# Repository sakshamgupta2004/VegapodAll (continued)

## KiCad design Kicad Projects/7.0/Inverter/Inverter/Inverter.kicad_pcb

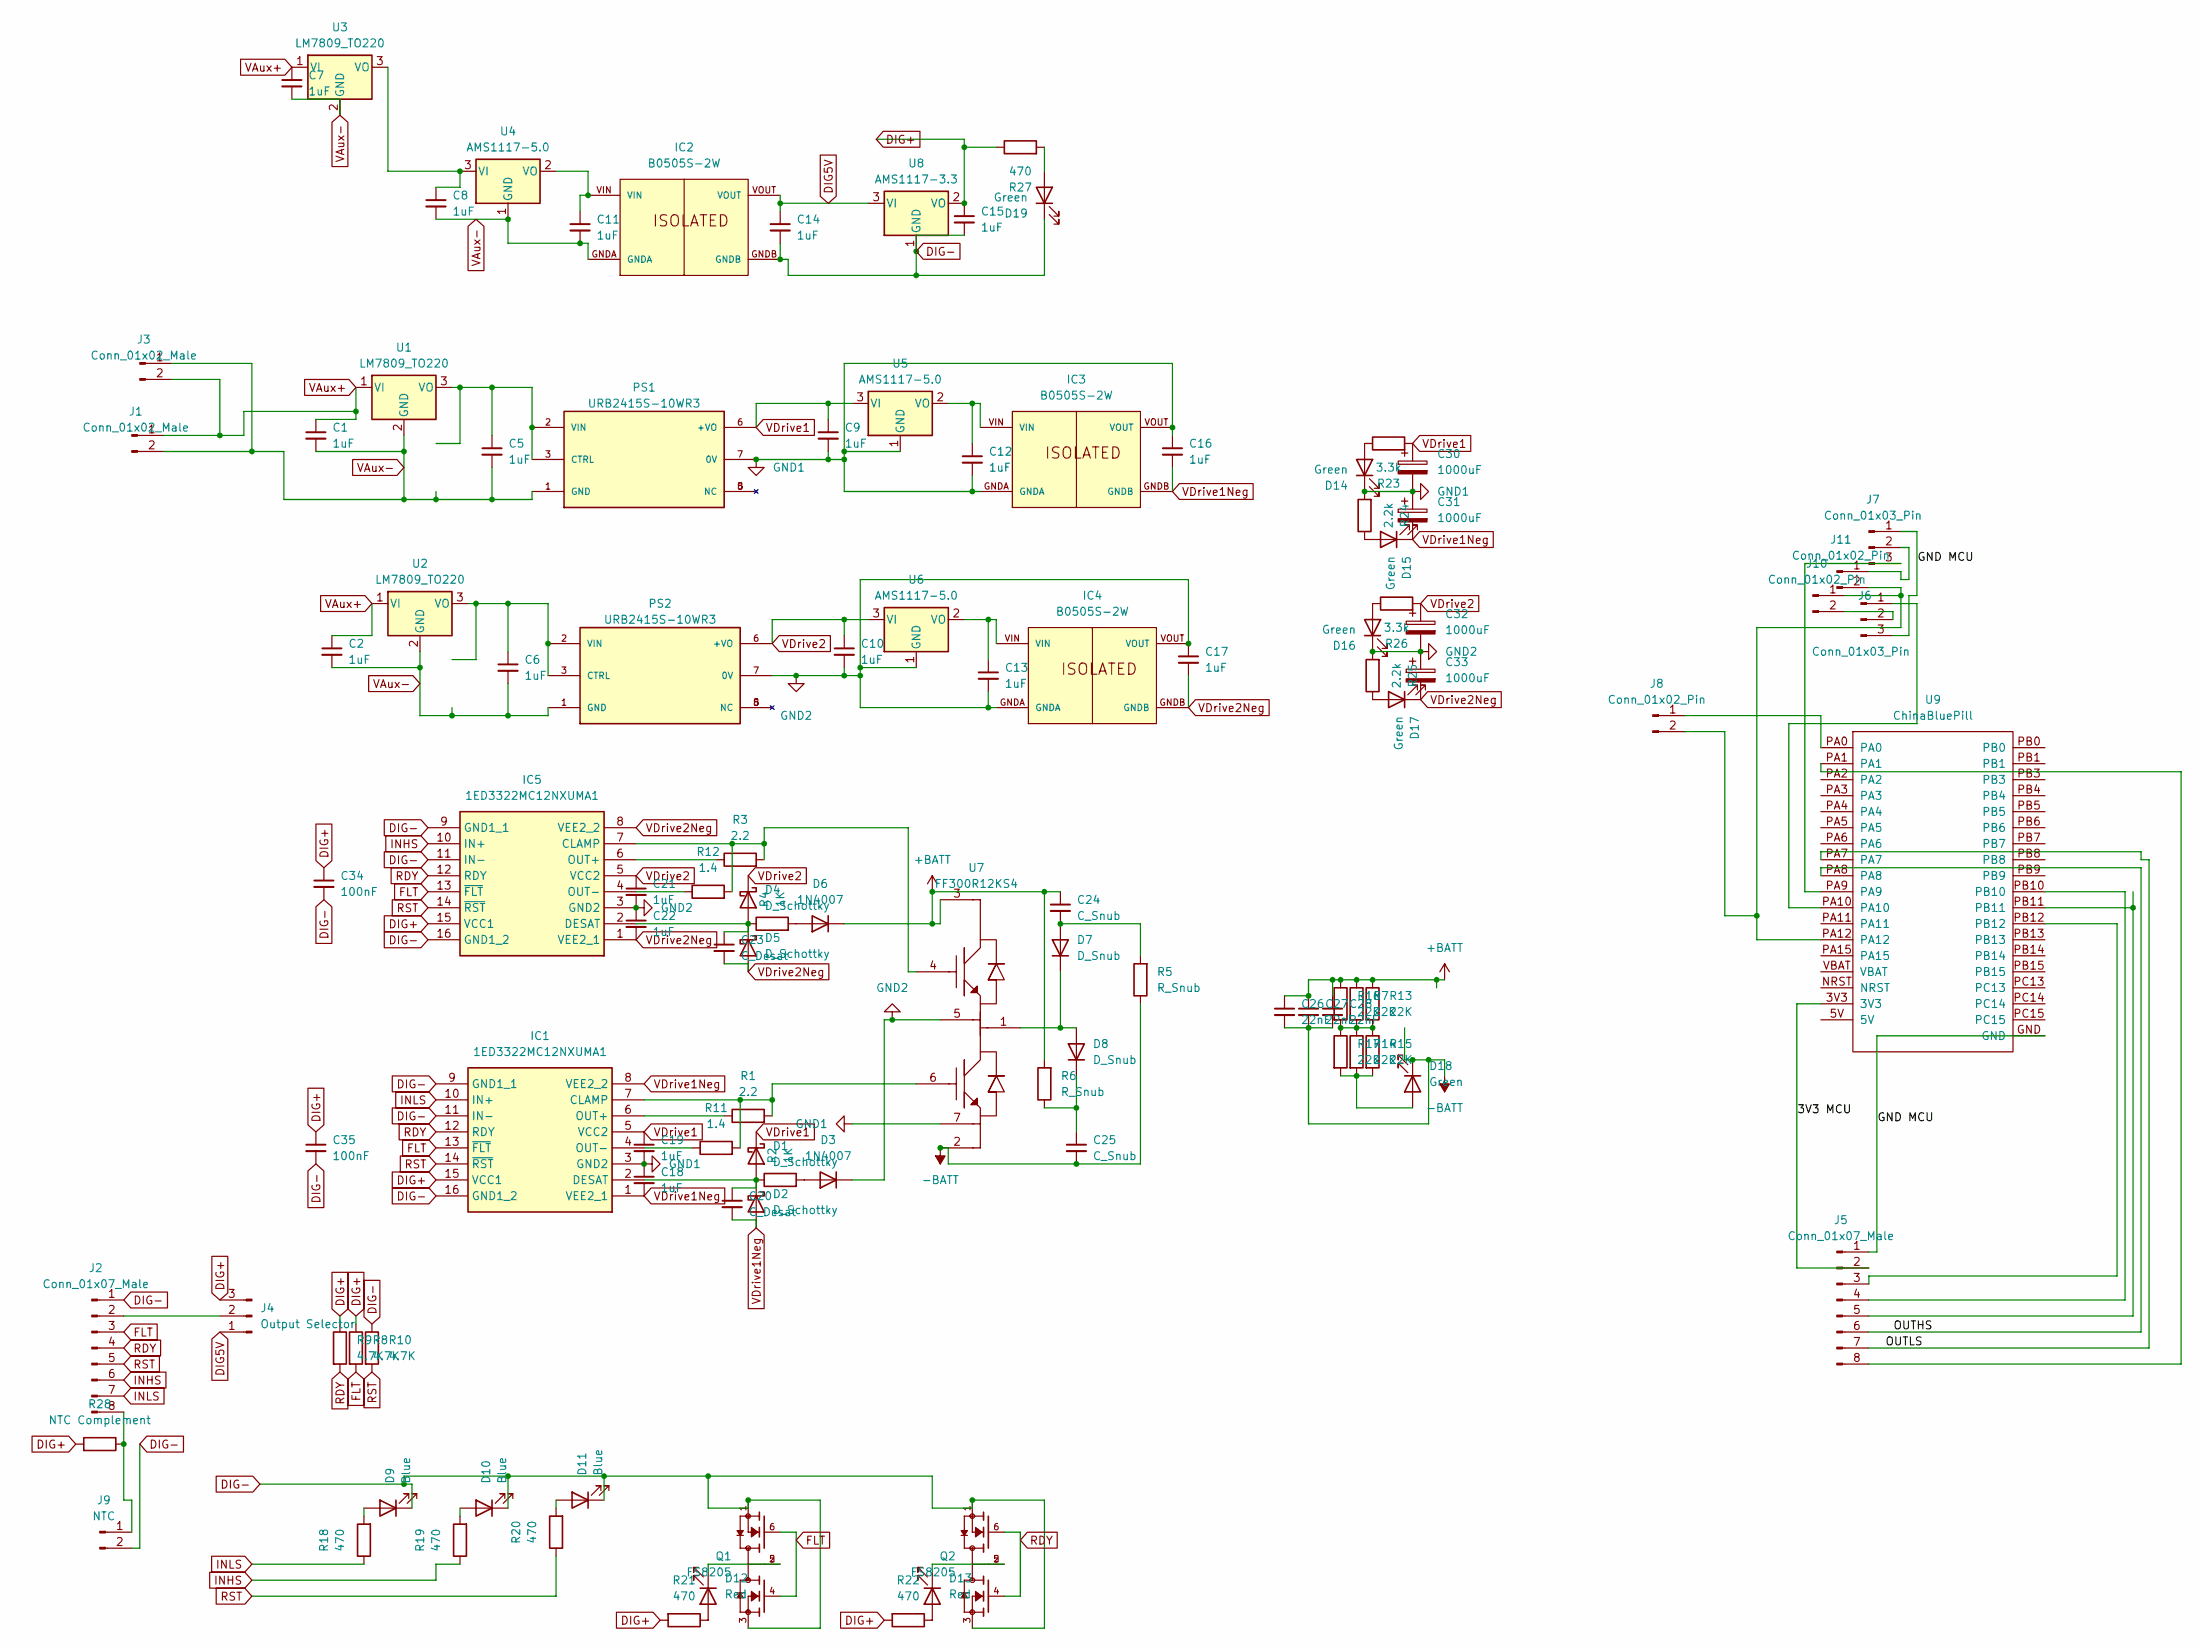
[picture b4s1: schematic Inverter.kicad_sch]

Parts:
C1, C2, C5, C6, C7, C8, C9, C10, C11, C12, C13, C14, C15, C16, C17, C18, C19, C21, C22: 1uF; C_1206_3216Metric_Pad1.33x1.80mm_HandSolder
C20, C23: C_Desat; C_0603_1608Metric_Pad1.08x0.95mm_HandSolder
C24, C25: C_Snub; C_Rect_L24.0mm_W8.3mm_P22.50mm_MKT
C26, C27, C28: 22nF; C_1206_3216Metric_Pad1.33x1.80mm_HandSolder
C30, C31, C32, C33: 1000uF; CAP_EEEFK1E102AQ
C34, C35: 100nF; C_0603_1608Metric_Pad1.08x0.95mm_HandSolder
D1, D2, D4, D5: D_Schottky; D_SMA_Handsoldering
D3, D6: 1N4007; D_SMA_Handsoldering
D7, D8: D_Snub; D_DO-201AE_P15.24mm_Horizontal
D9, D10, D11: Blue; LED_0805_2012Metric_Pad1.15x1.40mm_HandSolder
D12, D13: Red; LED_0805_2012Metric_Pad1.15x1.40mm_HandSolder
D14, D15, D16, D17, D18, D19: Green; LED_0805_2012Metric_Pad1.15x1.40mm_HandSolder
IC1, IC5: 1ED3322MC12NXUMA1; SOIC127P1030X265-16N; Mouser Part Number 726-1ED3322MC12NXUMA
IC2, IC3, IC4: B0505S-2W; MPN B0505S-2W; DigiKey_Part_Number 2725-B0505S-2W-ND
J1, J3: Conn_01x02_Male; JST_XH_S2B-XH-A_1x02_P2.50mm_Horizontal
J2, J5: Conn_01x07_Male; JST_XH_B8B-XH-A_1x08_P2.50mm_Vertical
J4: Output Selector; PinSocket_1x03_P1.27mm_Vertical
J6, J7: Conn_01x03_Pin; JST_XH_S3B-XH-A_1x03_P2.50mm_Horizontal
J8, J10, J11: Conn_01x02_Pin; PinHeader_1x02_P1.27mm_Vertical
J9: NTC; PinHeader_1x02_P1.27mm_Vertical
PS1, PS2: URB2415S-10WR3; CONV_URB2415S-10WR3; PARTREV 2020.11.09-A/4; DigiKey_Part_Number 2725-URB2415S-10WR3-ND
Q1, Q2: FS8205; SOT95P280X145-6N; PARTREV 1.9
R1, R3: 2.2; R_0805_2012Metric_Pad1.20x1.40mm_HandSolder
R2, R4: 1K; R_0603_1608Metric_Pad0.98x0.95mm_HandSolder
R5, R6: R_Snub; R_Box_L26.0mm_W5.0mm_P20.00mm
R7, R13, R14, R15, R16, R17: 22K; R_1206_3216Metric_Pad1.30x1.75mm_HandSolder
R8, R9, R10: 4.7K; R_0805_2012Metric_Pad1.20x1.40mm_HandSolder
R11, R12: 1.4; R_0805_2012Metric_Pad1.20x1.40mm_HandSolder
R18, R19, R20, R21, R22, R27: 470; R_0603_1608Metric_Pad0.98x0.95mm_HandSolder
R23, R26: 3.3k; R_0603_1608Metric_Pad0.98x0.95mm_HandSolder
R24, R25: 2.2k; R_0603_1608Metric_Pad0.98x0.95mm_HandSolder
R28: NTC Complement; R_0805_2012Metric_Pad1.20x1.40mm_HandSolder
U1, U2, U3: LM7809_TO220; TO-220-3_Vertical
U4, U5, U6: AMS1117-5.0; SOT-223-3_TabPin2
U7: FF300R12KS4
U8: AMS1117-3.3; SOT-223-3_TabPin2
U9: ChinaBluePill

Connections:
+BATT: C24.1, C26.1, C27.1, C28.1, D6.1 (K), R6.2, R7.1, R13.1, R16.1, U7.3
-BATT: C25.2, C26.2, C27.2, C28.2, D18.1 (K), R5.1, U7.2
/3V3 MCU: J5.2, U9.3V3
/GND MCU: J5.1, J6.3, J7.1, U9.GND
/OUTHS: J5.6, U9.PA8
/OUTLS: J5.7, U9.PA7
DIG5V: C14.1, IC2.VOUT, J4.1, U8.3 (VI)
DIG+: C15.1, C34.1, C35.1, IC1.15 (VCC1), IC5.15 (VCC1), J4.3, R8.1, R9.1, R21.2, R22.2, R27.1, R28.2, U8.2 (VO)
DIG-: C14.2, C15.2, C34.2, C35.2, D9.1 (K), D10.1 (K), D11.1 (K), D19.1 (K), IC1.9 (GND1_1), IC1.11 (IN-), IC1.16 (GND1_2), IC2.GNDB, IC5.9 (GND1_1), IC5.11 (IN-), IC5.16 (GND1_2), J2.1, J9.2, Q1.1, Q1.3, Q2.1, Q2.3, R10.1, U8.1 (GND)
FLT: IC1.13 (~FLT), IC5.13 (~FLT), J2.3, Q1.4, Q1.6, R8.2
GND1: C9.2, C12.2, C16.1, C18.1, C19.2, C30.2, C31.1, D14.1 (K), IC1.3 (GND2), IC3.GNDA, IC3.VOUT, PS1.7 (0V), R24.2, U5.1 (GND), U7.7
GND2: C10.2, C13.2, C17.1, C21.2, C22.1, C32.2, C33.1, D3.1 (K), D16.1 (K), IC4.GNDA, IC4.VOUT, IC5.3 (GND2), PS2.7 (0V), R25.2, U6.1 (GND), U7.5
INHS: IC5.10 (IN+), J2.6, R19.1
INLS: IC1.10 (IN+), J2.7, R18.1
unnamed: C20.1, D1.2 (A), D2.1 (K), IC1.2 (DESAT), R2.1
unnamed: D3.2 (A), R2.2
unnamed: C23.1, D4.2 (A), D5.1 (K), IC5.2 (DESAT), R4.1
unnamed: D6.2 (A), R4.2
unnamed: C24.2, D7.2 (A), R5.2
unnamed: D7.1 (K), D8.2 (A), U7.1
unnamed: C25.1, D8.1 (K), R6.1
unnamed: D9.2 (A), R18.2
unnamed: D10.2 (A), R19.2
unnamed: D11.2 (A), R20.2
unnamed: D12.2 (A), R21.1
unnamed: D12.1 (K), Q1.2, Q1.5
unnamed: D13.2 (A), R22.1
unnamed: D13.1 (K), Q2.2, Q2.5
unnamed: D14.2 (A), R23.1
unnamed: D15.2 (A), R24.1
unnamed: D16.2 (A), R26.1
unnamed: D17.2 (A), R25.1
unnamed: D18.2 (A), R14.2, R15.2, R17.2
unnamed: D19.2 (A), R27.2
unnamed: IC1.7 (CLAMP), R1.2, R11.2, U7.6
unnamed: IC1.6 (OUT+), R1.1
unnamed: IC1.4 (OUT-), R11.1
unnamed: IC5.7 (CLAMP), R3.2, R12.2, U7.4
unnamed: IC5.6 (OUT+), R3.1
unnamed: IC5.4 (OUT-), R12.1
unnamed: J2.2, J4.2
unnamed: J2.8, J9.1, R28.1
unnamed: J5.3, U9.PB12
unnamed: J5.4, U9.PB10
unnamed: J5.5, U9.PB11
unnamed: J5.8, U9.PA1
unnamed: J6.1, U9.PA10
unnamed: J7.3, U9.PA9
unnamed: J8.1, U9.PA0
unnamed: J8.2, J10.1, J11.2, U9.PA12
unnamed: J6.2, J10.2
unnamed: J7.2, J11.1
unnamed: C5.1, PS1.2 (VIN), PS1.3 (CTRL), U1.3 (VO)
unnamed: C6.1, PS2.2 (VIN), PS2.3 (CTRL), U2.3 (VO)
unnamed: R7.2, R13.2, R14.1, R15.1, R16.2, R17.1
unnamed: C8.1, U3.3 (VO), U4.3 (VI)
unnamed: C11.1, IC2.VIN, U4.2 (VO)
unnamed: C12.1, IC3.VIN, U5.2 (VO)
unnamed: C13.1, IC4.VIN, U6.2 (VO)
RDY: IC1.12 (RDY), IC5.12 (RDY), J2.4, Q2.4, Q2.6, R9.2
RST: IC1.14 (~RST), IC5.14 (~RST), J2.5, R10.2, R20.1
VAux+: C1.1, C2.1, C7.1, J1.1, J3.2, U1.1 (VI), U2.1 (VI), U3.1 (VI)
VAux-: C1.2, C2.2, C5.2, C6.2, C7.2, C8.2, C11.2, IC2.GNDA, J1.2, J3.1, PS1.1 (GND), PS2.1 (GND), U1.2 (GND), U2.2 (GND), U3.2 (GND), U4.1 (GND)
VDrive1: C9.1, C19.1, C30.1, D1.1 (K), IC1.5 (VCC2), PS1.6 (+VO), R23.2, U5.3 (VI)
VDrive1Neg: C16.2, C18.2, C20.2, C31.2, D2.2 (A), D15.1 (K), IC1.1 (VEE2_1), IC1.8 (VEE2_2), IC3.GNDB
VDrive2: C10.1, C21.1, C32.1, D4.1 (K), IC5.5 (VCC2), PS2.6 (+VO), R26.2, U6.3 (VI)
VDrive2Neg: C17.2, C22.2, C23.2, C33.2, D5.2 (A), D17.1 (K), IC4.GNDB, IC5.1 (VEE2_1), IC5.8 (VEE2_2)

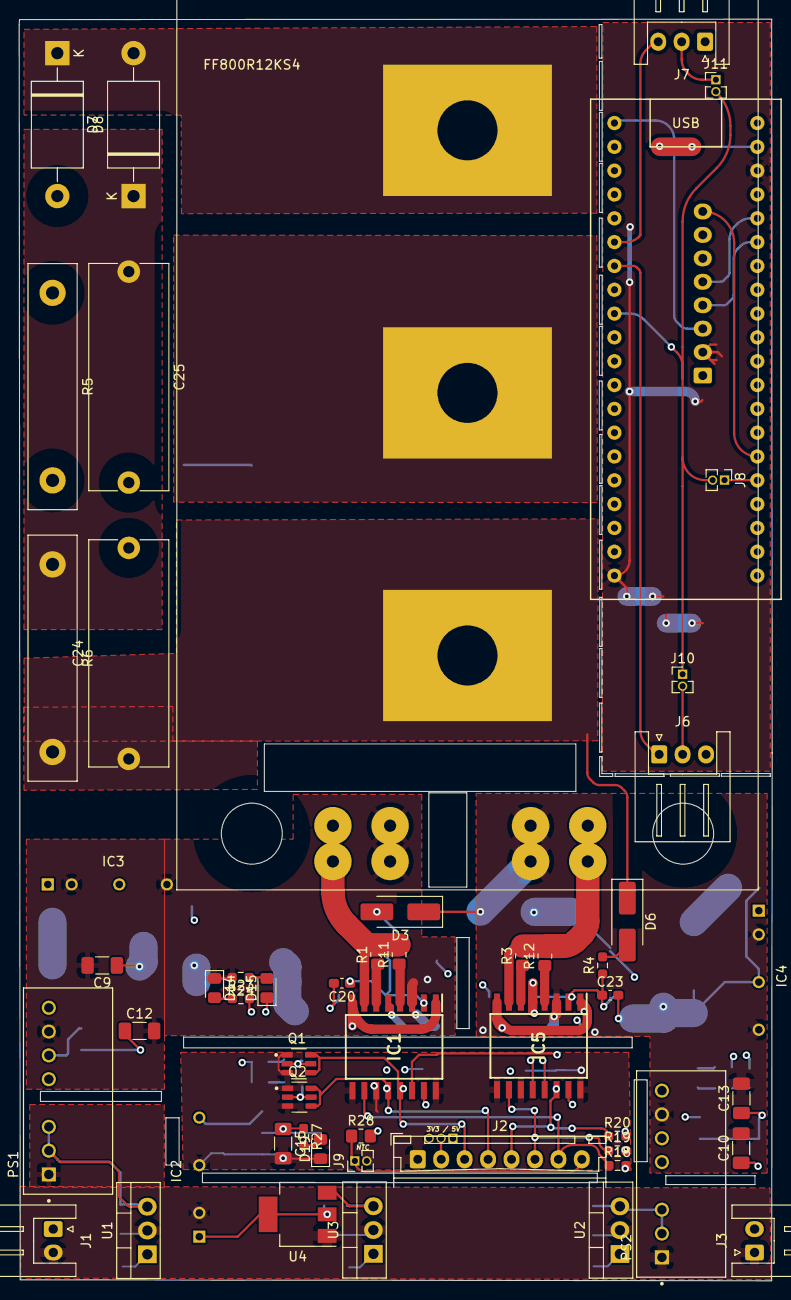
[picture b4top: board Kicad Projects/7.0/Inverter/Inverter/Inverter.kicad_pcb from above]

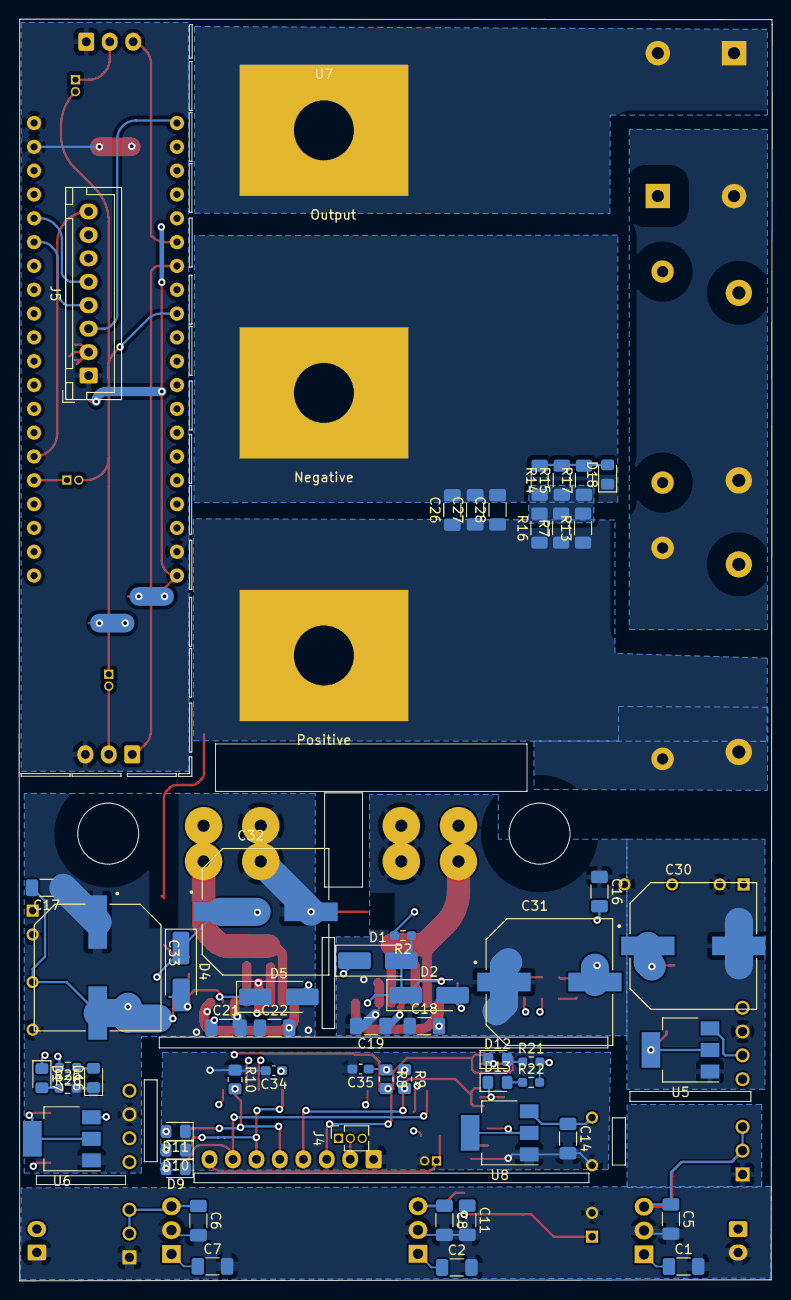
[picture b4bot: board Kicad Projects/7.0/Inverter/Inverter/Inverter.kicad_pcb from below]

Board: 4 copper layers, 80.3 x 134.5 mm, 108 parts (55 on the bottom side), 67 nets.

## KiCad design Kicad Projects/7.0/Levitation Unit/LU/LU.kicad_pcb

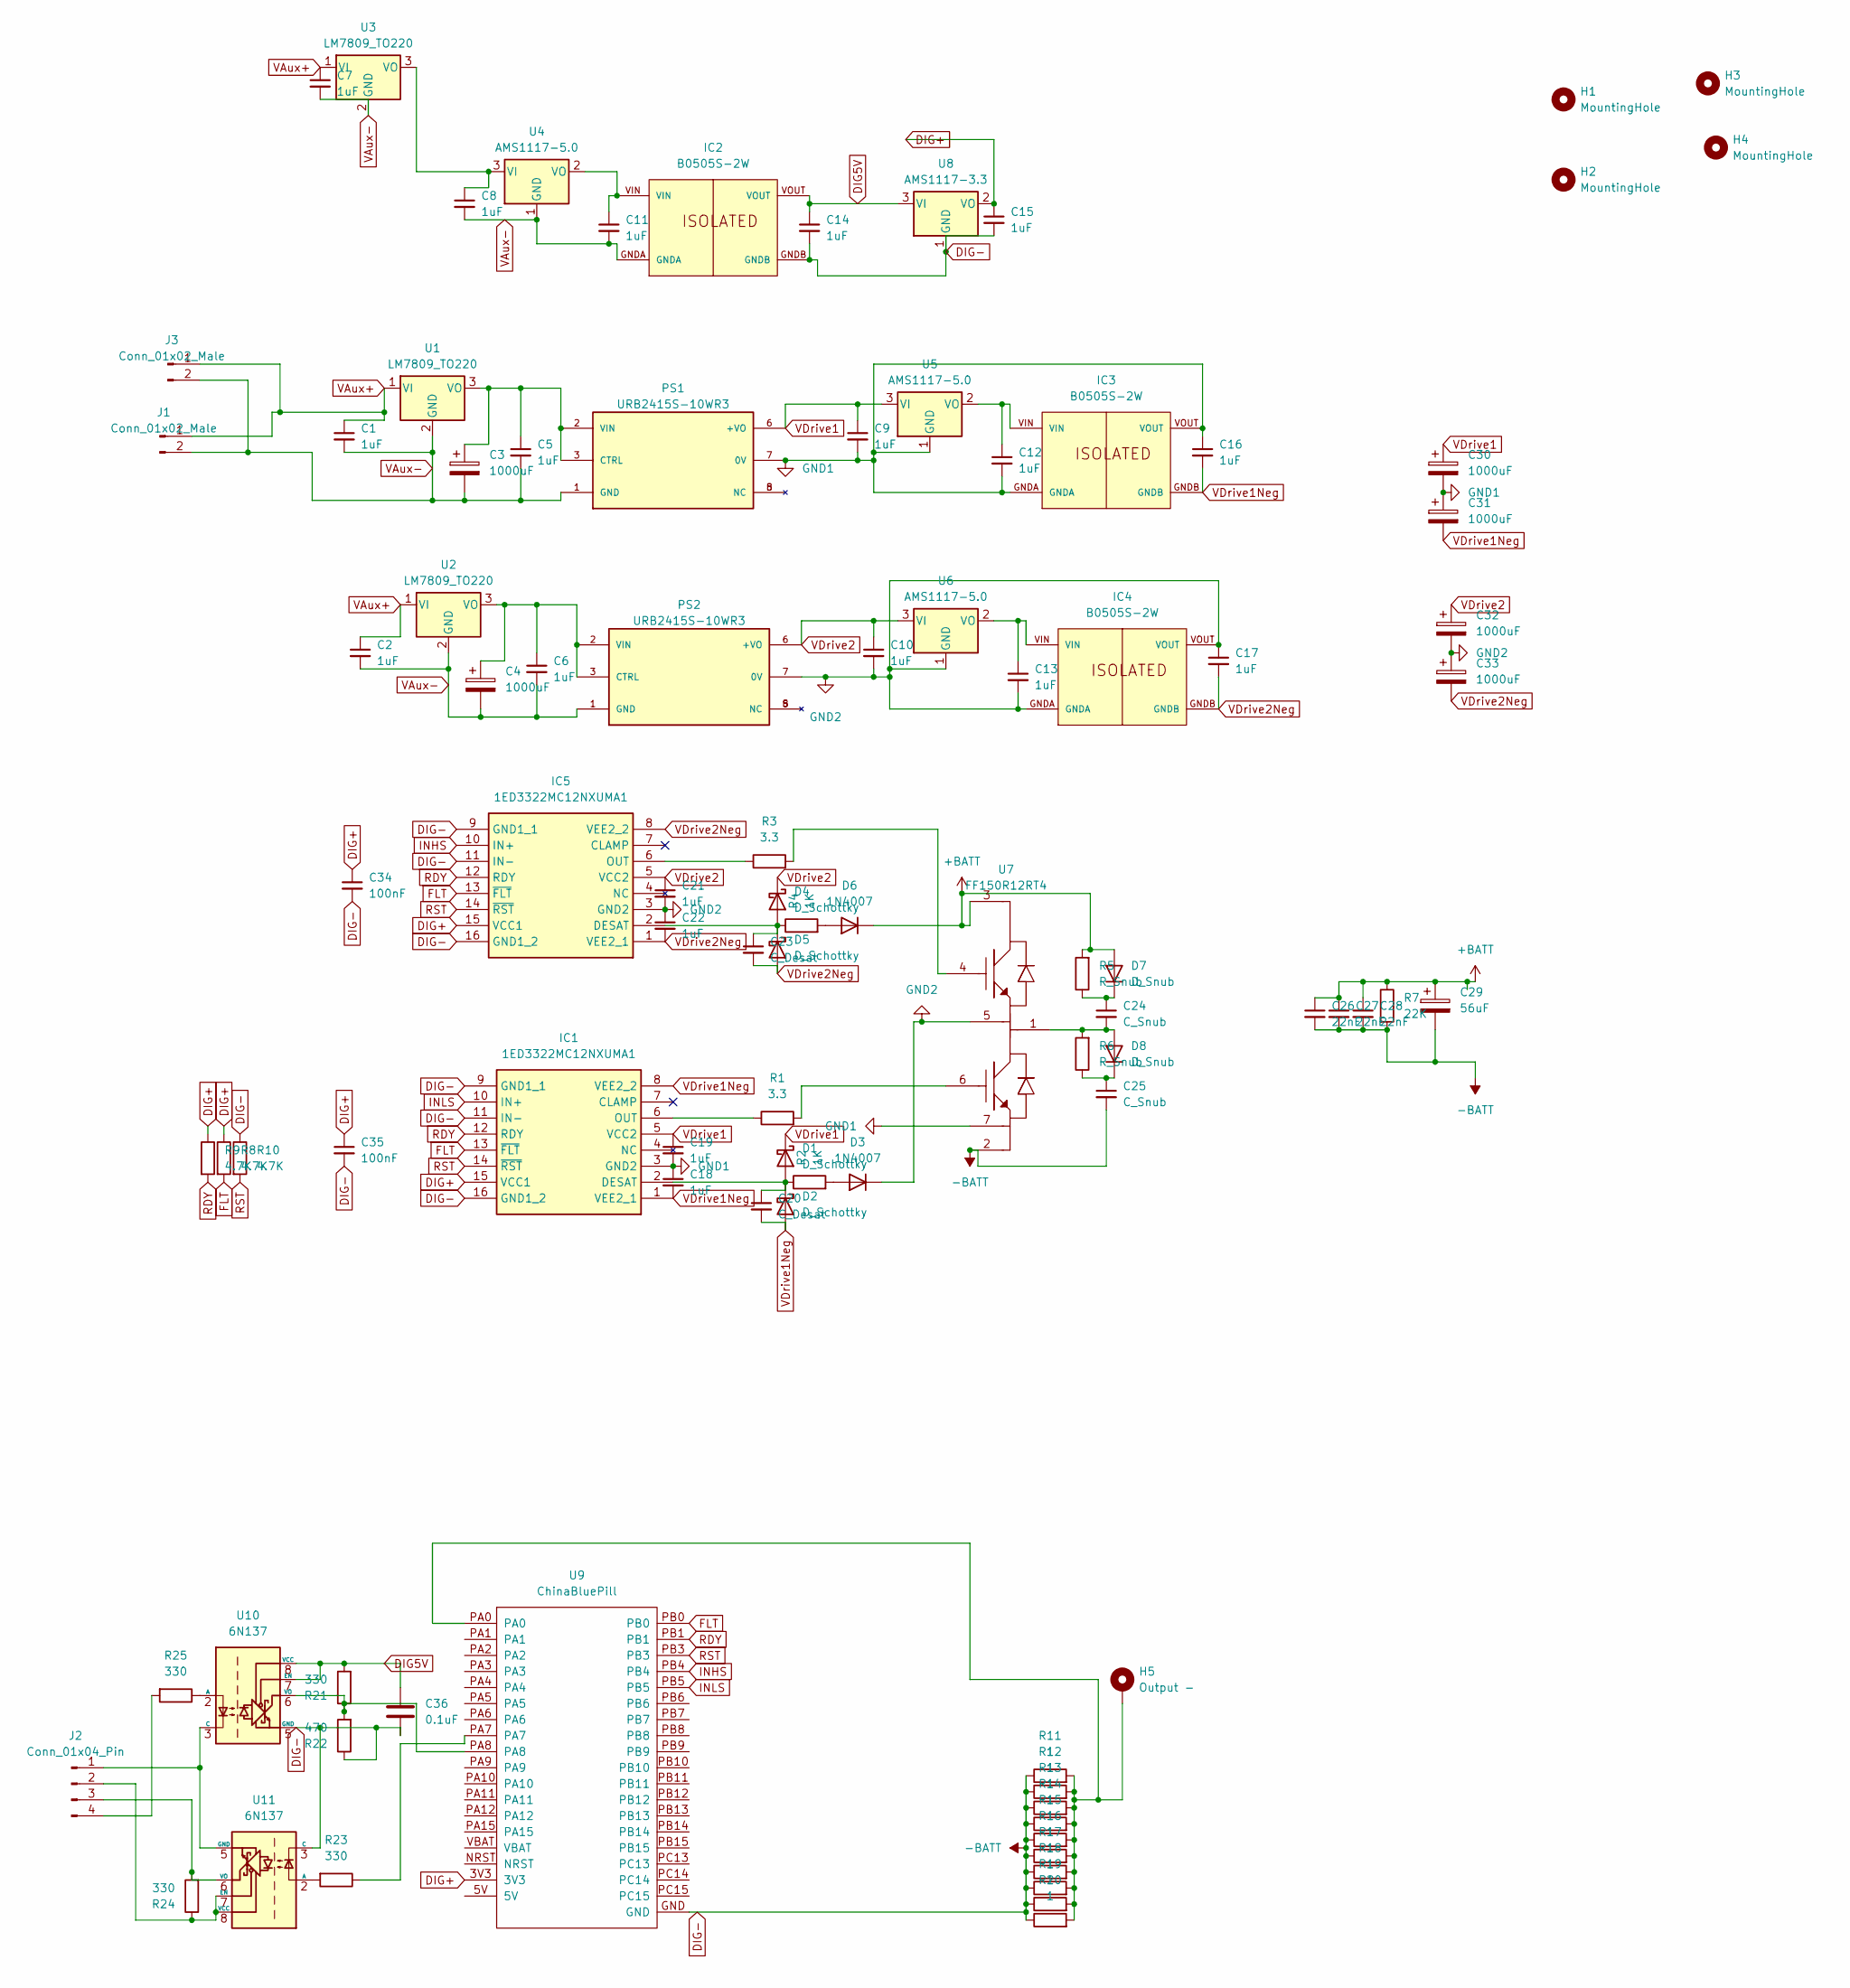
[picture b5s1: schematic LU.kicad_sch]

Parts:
C1, C2, C5, C6, C7, C8, C9, C10, C11, C12, C13, C14, C15, C16, C17, C18, C19, C21, C22: 1uF; C_1206_3216Metric_Pad1.33x1.80mm_HandSolder
C3, C4, C30, C31, C32, C33: 1000uF; CAP_EEEFK1E102AQ
C20, C23: C_Desat; C_0603_1608Metric_Pad1.08x0.95mm_HandSolder
C24, C25: C_Snub; C_Rect_L24.0mm_W8.3mm_P22.50mm_MKT
C26, C27, C28: 22nF; C_1206_3216Metric_Pad1.33x1.80mm_HandSolder
C29: 56uF; CP_Radial_D16.0mm_P7.50mm
C34, C35: 100nF; C_0603_1608Metric_Pad1.08x0.95mm_HandSolder
C36: 0.1uF; C_0201_0603Metric_Pad0.64x0.40mm_HandSolder
D1, D2, D4, D5: D_Schottky; D_SMA_Handsoldering
D3, D6: 1N4007; D_SMA_Handsoldering
D7, D8: D_Snub; D_DO-201AE_P15.24mm_Horizontal
H1, H2, H3, H4: MountingHole; MountingHole_3.2mm_M3
H5: Output -; MountingHole_6.4mm_M6_Pad
IC1, IC5: 1ED3322MC12NXUMA1; SOIC127P1030X265-16N; Mouser Part Number 726-1ED3322MC12NXUMA
IC2, IC3, IC4: B0505S-2W; MPN B0505S-2W; DigiKey_Part_Number 2725-B0505S-2W-ND
J1, J3: Conn_01x02_Male; JST_XH_S2B-XH-A_1x02_P2.50mm_Horizontal
J2: Conn_01x04_Pin; JST_XH_B4B-XH-AM_1x04_P2.50mm_Vertical
PS1, PS2: URB2415S-10WR3; CONV_URB2415S-10WR3; PARTREV 2020.11.09-A/4; DigiKey_Part_Number 2725-URB2415S-10WR3-ND
R1, R3: 3.3; R_0805_2012Metric_Pad1.20x1.40mm_HandSolder
R2, R4: 1K; R_0603_1608Metric_Pad0.98x0.95mm_HandSolder
R5, R6: R_Snub; R_Box_L26.0mm_W5.0mm_P20.00mm
R7: 22K; R_1206_3216Metric_Pad1.30x1.75mm_HandSolder
R8, R9, R10: 4.7K; R_0805_2012Metric_Pad1.20x1.40mm_HandSolder
R11, R12, R13, R14, R15, R16, R17, R18, R19, R20: 1; R_2512_6332Metric_Pad1.40x3.35mm_HandSolder
R21, R23, R24, R25: 330; R_0201_0603Metric_Pad0.64x0.40mm_HandSolder
R22: 470; R_0201_0603Metric_Pad0.64x0.40mm_HandSolder
U1, U2, U3: LM7809_TO220; TO-220-3_Vertical
U4, U5, U6: AMS1117-5.0; SOT-223-3_TabPin2
U7: FF150R12RT4; FF300R12KS4
U8: AMS1117-3.3; SOT-223-3_TabPin2
U9: ChinaBluePill
U10, U11: 6N137; DIP-8_W7.62mm

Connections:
+BATT: C26.1, C27.1, C28.1, C29.1, D6.1 (K), D7.2 (A), R5.2, R7.1, U7.3
DIG5V: C14.1, C36.1, IC2.VOUT, R21.2, U8.3 (VI), U10.7 (EN), U10.8 (VCC)
DIG+: C15.1, C34.1, C35.1, IC1.15 (VCC1), IC5.15 (VCC1), R8.1, R9.1, U8.2 (VO), U9.3V3
DIG-: C14.2, C15.2, C25.2, C26.2, C27.2, C28.2, C29.2, C34.2, C35.2, C36.2, IC1.9 (GND1_1), IC1.11 (IN-), IC1.16 (GND1_2), IC2.GNDB, IC5.9 (GND1_1), IC5.11 (IN-), IC5.16 (GND1_2), R7.2, R10.1, R11.1, R12.1, R13.1, R14.1, R15.1, R16.1, R17.1, R18.1, R19.1, R20.1, R22.1, U7.2, U8.1 (GND), U9.GND, U10.5 (GND), U11.3 (C)
FLT: IC1.13 (~FLT), IC5.13 (~FLT), R8.2, U9.PB0
GND1: C9.2, C12.2, C16.1, C18.1, C19.2, C30.2, C31.1, IC1.3 (GND2), IC3.GNDA, IC3.VOUT, PS1.7 (0V), U5.1 (GND), U7.7
GND2: C10.2, C13.2, C17.1, C21.2, C22.1, C32.2, C33.1, D3.1 (K), IC4.GNDA, IC4.VOUT, IC5.3 (GND2), PS2.7 (0V), U6.1 (GND), U7.5
INHS: IC5.10 (IN+), U9.PB4
INLS: IC1.10 (IN+), U9.PB5
unnamed: C20.1, D1.2 (A), D2.1 (K), IC1.2 (DESAT), R2.1
unnamed: D3.2 (A), R2.2
unnamed: C23.1, D4.2 (A), D5.1 (K), IC5.2 (DESAT), R4.1
unnamed: D6.2 (A), R4.2
unnamed: C24.1, D7.1 (K), R5.1
unnamed: C24.2, D8.2 (A), R6.2, U7.1
unnamed: C25.1, D8.1 (K), R6.1
unnamed: H5.1, R11.2, R12.2, R13.2, R14.2, R15.2, R16.2, R17.2, R18.2, R19.2, R20.2, U9.PA0
unnamed: IC1.6 (OUT), R1.1
unnamed: IC5.6 (OUT), R3.1
unnamed: J2.1, U10.3 (C), U11.5 (GND)
unnamed: J2.2, R24.1, U11.7 (EN), U11.8 (VCC)
unnamed: J2.3, R24.2, U11.6 (VO)
unnamed: J2.4, R25.2
unnamed: C3.1, C5.1, PS1.2 (VIN), PS1.3 (CTRL), U1.3 (VO)
unnamed: C4.1, C6.1, PS2.2 (VIN), PS2.3 (CTRL), U2.3 (VO)
unnamed: R1.2, U7.6
unnamed: R3.2, U7.4
unnamed: R23.1, U9.PA7
unnamed: C8.1, U3.3 (VO), U4.3 (VI)
unnamed: C11.1, IC2.VIN, U4.2 (VO)
unnamed: C12.1, IC3.VIN, U5.2 (VO)
unnamed: C13.1, IC4.VIN, U6.2 (VO)
unnamed: R25.1, U10.2 (A)
unnamed: R21.1, R22.2, U9.PA8, U10.6 (VO)
unnamed: R23.2, U11.2 (A)
RDY: IC1.12 (RDY), IC5.12 (RDY), R9.2, U9.PB1
RST: IC1.14 (~RST), IC5.14 (~RST), R10.2, U9.PB3
VAux+: C1.1, C2.1, C7.1, J1.1, J3.1, U1.1 (VI), U2.1 (VI), U3.1 (VI)
VAux-: C1.2, C2.2, C3.2, C4.2, C5.2, C6.2, C7.2, C8.2, C11.2, IC2.GNDA, J1.2, J3.2, PS1.1 (GND), PS2.1 (GND), U1.2 (GND), U2.2 (GND), U3.2 (GND), U4.1 (GND)
VDrive1: C9.1, C19.1, C30.1, D1.1 (K), IC1.5 (VCC2), PS1.6 (+VO), U5.3 (VI)
VDrive1Neg: C16.2, C18.2, C20.2, C31.2, D2.2 (A), IC1.1 (VEE2_1), IC1.8 (VEE2_2), IC3.GNDB
VDrive2: C10.1, C21.1, C32.1, D4.1 (K), IC5.5 (VCC2), PS2.6 (+VO), U6.3 (VI)
VDrive2Neg: C17.2, C22.2, C23.2, C33.2, D5.2 (A), IC4.GNDB, IC5.1 (VEE2_1), IC5.8 (VEE2_2)

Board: 2 copper layers, 95 parts (0 on the bottom side), 43 nets, no tracks yet.

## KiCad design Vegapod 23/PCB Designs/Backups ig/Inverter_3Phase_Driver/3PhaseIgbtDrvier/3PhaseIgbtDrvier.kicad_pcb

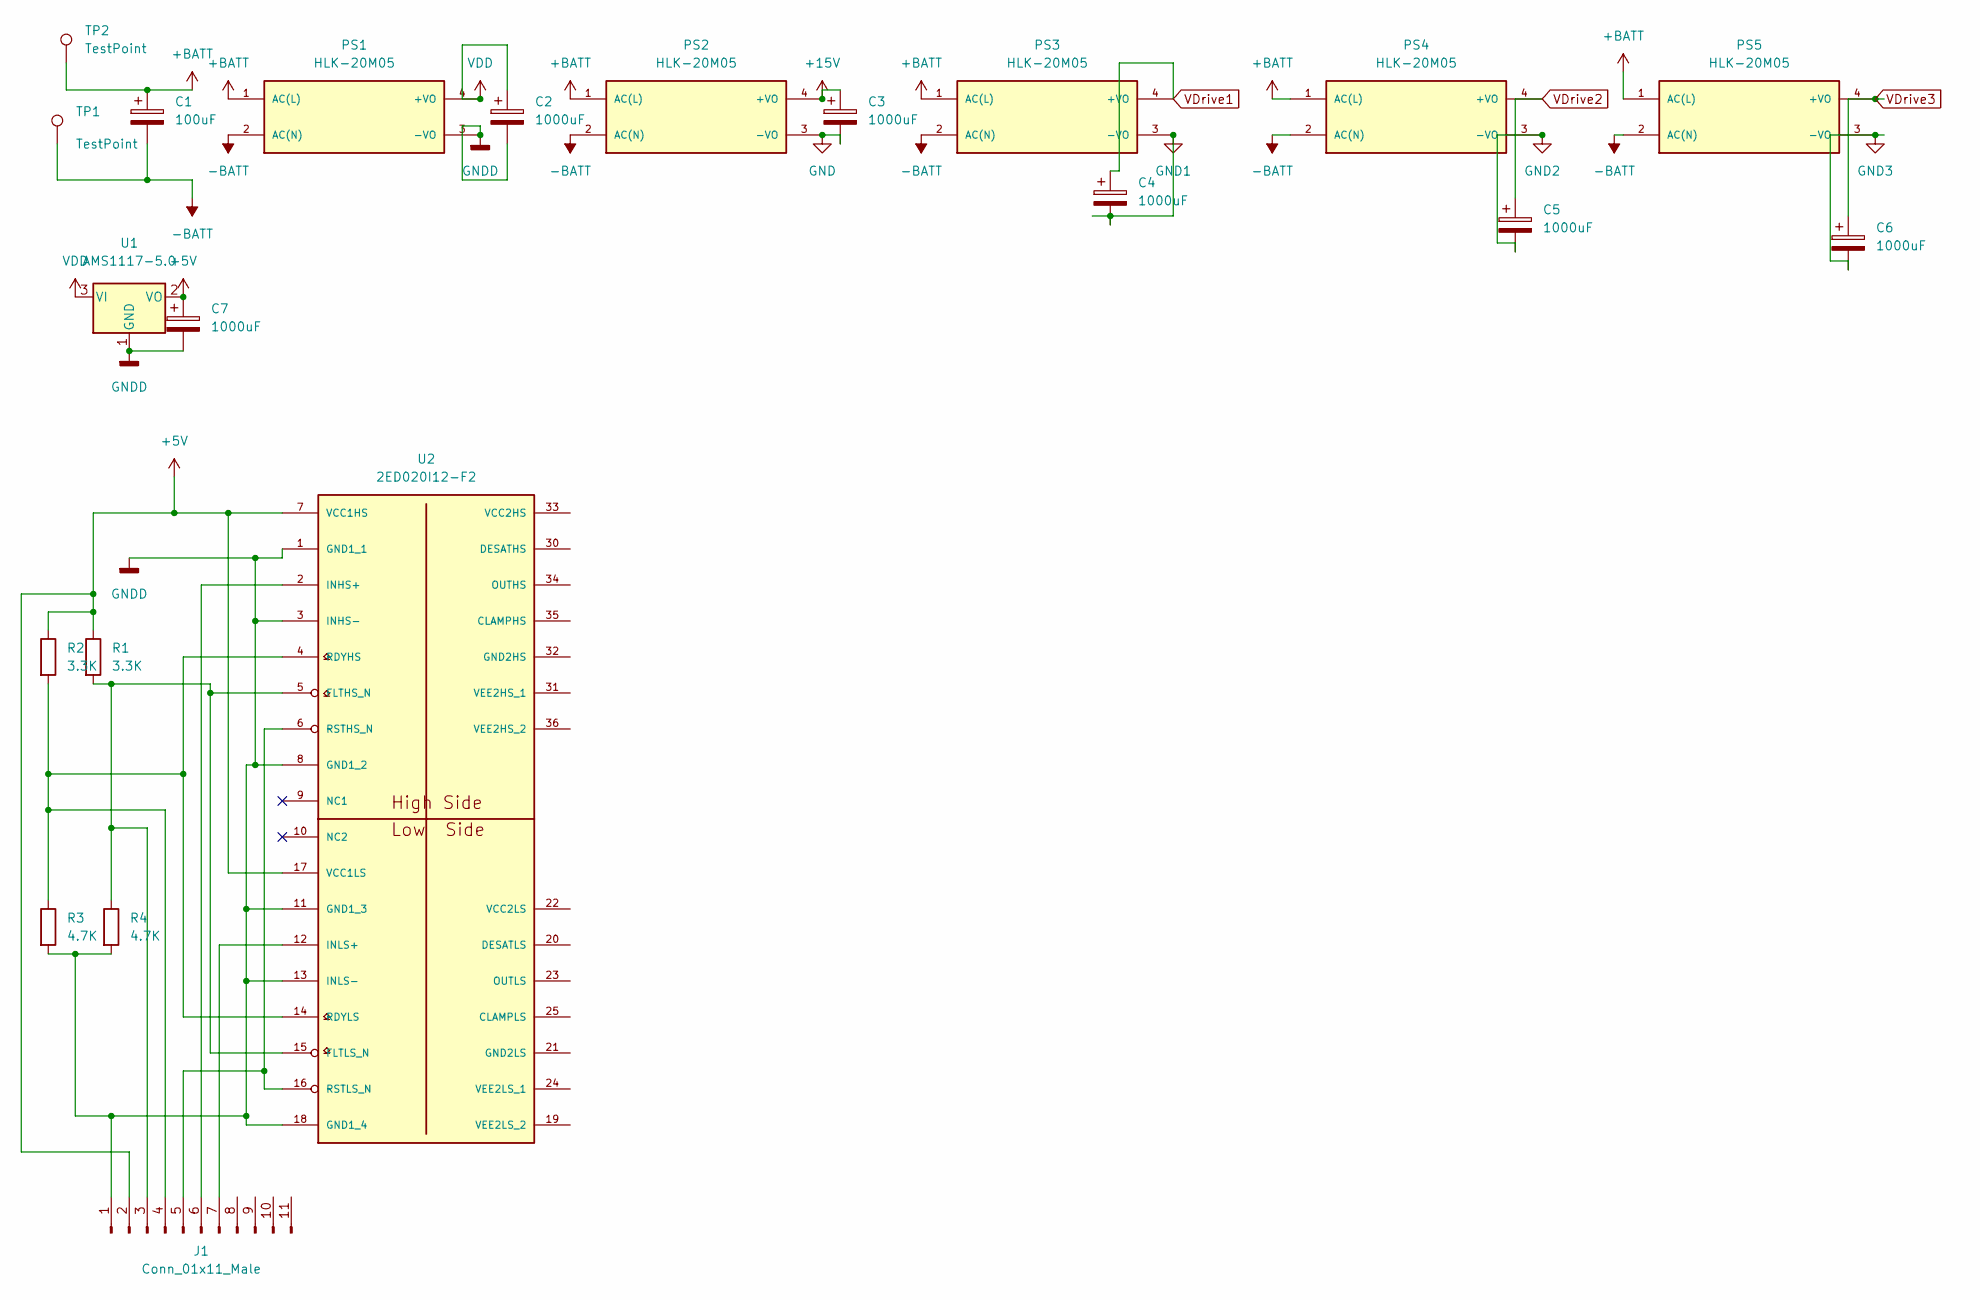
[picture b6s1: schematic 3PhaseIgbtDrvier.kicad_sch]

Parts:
C1: 100uF; CP_Radial_D8.0mm_P5.00mm
C2, C3, C4, C5, C6, C7: 1000uF; CP_Radial_D8.0mm_P5.00mm
J1: Conn_01x11_Male; PinHeader_1x11_P2.54mm_Vertical
PS1, PS2, PS3, PS4, PS5: HLK-20M05; CONV_HLK-20M05; PARTREV V1.3
R1, R2: 3.3K; R_Axial_DIN0411_L9.9mm_D3.6mm_P12.70mm_Horizontal
R3, R4: 4.7K; R_Axial_DIN0411_L9.9mm_D3.6mm_P12.70mm_Horizontal
TP1, TP2: TestPoint; TestPoint_Pad_D3.0mm
U1: AMS1117-5.0; SOT-223-3_TabPin2
U2: 2ED020I12-F2; SOP65P1030X265-36_32N-V

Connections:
+5V: C7.1, J1.2, R1.1, R2.1, U1.2 (VO), U2.7 (VCC1HS), U2.17 (VCC1LS)
+15V: C3.1, PS2.4 (+VO)
+BATT: C1.1, PS1.1 (AC(L)), PS2.1 (AC(L)), PS3.1 (AC(L)), PS4.1 (AC(L)), PS5.1 (AC(L)), TP2.1
-BATT: C1.2, PS1.2 (AC(N)), PS2.2 (AC(N)), PS3.2 (AC(N)), PS4.2 (AC(N)), PS5.2 (AC(N)), TP1.1
GND: C3.2, PS2.3 (-VO)
GND1: C4.2, PS3.3 (-VO)
GND2: C5.2, PS4.3 (-VO)
GND3: C6.2, PS5.3 (-VO)
GNDD: C2.2, C7.2, J1.1, PS1.3 (-VO), R3.2, R4.2, U1.1 (GND), U2.1 (GND1_1), U2.3 (INHS-), U2.8 (GND1_2), U2.11 (GND1_3), U2.13 (INLS-), U2.18 (GND1_4)
unnamed: J1.3, R1.2, R4.1, U2.5 (FLTHS_N), U2.15 (FLTLS_N)
unnamed: J1.4, R2.2, R3.1, U2.4 (RDYHS), U2.14 (RDYLS)
unnamed: J1.5, U2.6 (RSTHS_N), U2.16 (RSTLS_N)
unnamed: J1.6, U2.2 (INHS+)
unnamed: J1.7, U2.12 (INLS+)
VDD: C2.1, PS1.4 (+VO), U1.3 (VI)
VDrive1: C4.1, PS3.4 (+VO)
VDrive2: C5.1, PS4.4 (+VO)
VDrive3: C6.1, PS5.4 (+VO)

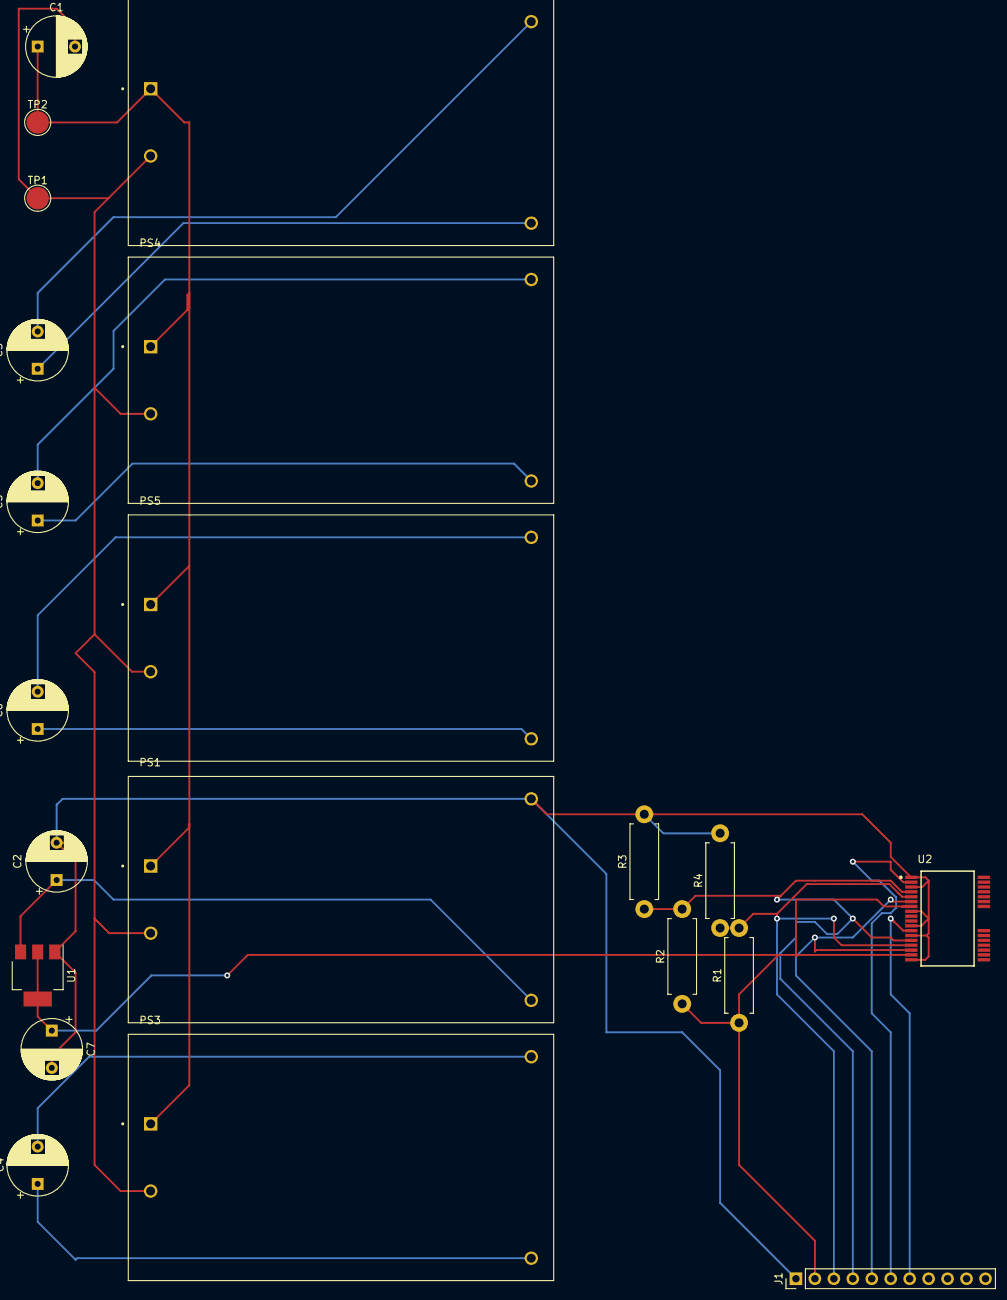
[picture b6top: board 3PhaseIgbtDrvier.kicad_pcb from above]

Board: 2 copper layers, 21 parts (0 on the bottom side), 18 nets.
